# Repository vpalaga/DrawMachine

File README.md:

# DrawMachine

**An XY pen plotter driven by a Raspberry Pi Pico and a home-made G-code dialect called FCODE.**

Feed it a `.dxf` drawing, it works out where the pen has to go, and a Pico steps three stepper motors (X, Y and a Z pen lift) to draw it on A4 paper.

> **The goal:** a 100% working, reliable XY plotter that does my homework.
> Partially based on the Scrabble bot.

---

## How it works

```mermaid
flowchart LR
    A[".dxf drawing"] --> B["FCODEgenerator<br/>Python"]
    B --> C[".FCODE file<br/>absolute positions in mm"]
    C --> D["DataSendToPico<br/>Python, over USB serial"]
    D --> E["Pico firmware<br/>C++, relative steps"]
    E --> F["TMC2209 drivers<br/>X, Y, Z steppers"]
```

1. **`FCODEgenerator`** reads a DXF (or you script the pen by hand), centres it on the paper, reorders the strokes to minimise pen travel, and writes an `.FCODE` text file. Positions are in **millimetres**.
2. **`DataSendToPico`** reads the FCODE file line by line, converts millimetres to motor steps, range-checks every move and sends one command at a time to the Pico over USB CDC (virtual serial port). It waits for the Pico to confirm each command.
3. **`StepperDriver-pico`** is the firmware. It parses each command, coordinates X and Y step pulses so both axes finish a move together, lifts and lowers the pen, and homes against the end switches.

---

## Repository layout

| Path | What's in it |
| --- | --- |
| `FCODEgenerator/` | DXF reader, path optimiser, FCODE writer and preview renderer (Python) |
| `FCODEgenerator/dxfexamples/` | Sample DXF files to try |
| `DataSendToPico/` | Host-side sender: file runner, mm to steps conversion, serial transport, test CLI and GUI (Python) |
| `StepperDriver-pico/` | Pico firmware (C++ / Pico SDK) |
| `StepperDriver-pico/Pico_pins_map.txt` | ASCII Pico pinout showing which GPIO does what |
| `StepperDriver-pico/bresenham_test.py` | Draws the step pattern of the line algorithm with PIL, used to design the move function |
| `pcb/2.0/DrawMv2.0/` | **Current board**: KiCad project for the v2.0 controller PCB |
| `pcb/test/` | Retired first prototype board (v1), kept for reference only |
| `pcb2_0_schematic.pdf` | PDF of the v2.0 schematic |
| `images/` | Documentation images |

---

## Hardware

- **Controller:** Raspberry Pi Pico (USB CDC serial to the PC).
- **Drivers:** three **TMC2209** stepper drivers, one each for X, Y and Z. Microstepping is set on the board with switches, and the host software assumes **8x**.
- **Motion:** 200 steps/rev steppers on 2 mm pitch rods, so the host uses **800 steps per mm** (200 x 8 microsteps / 2 mm).
- **Pen lift:** the Z stepper raises and lowers the pen. The default stroke is 6500 steps and can be changed with `SZS`.
- **Limit switches:** one each for X, Y and Z, used for calibration. Each limit-switch input has an external 4.7 kΩ pull-up resistor.
- **Work area:** A4 landscape, 297 x 210 mm (A5 and A3 are also defined in the generator).
- **Indicators:** an "instruction" LED (lit while commands are arriving) and a "console mode" LED.
- **Board extras (v2.0):** 6 A fuse and bulk capacitor on the motor supply, status LEDs and a debug header.

### Pin map (from `motorDriver.cpp`)

A full ASCII drawing of the Pico with every pin is in [`StepperDriver-pico/Pico_pins_map.txt`](StepperDriver-pico/Pico_pins_map.txt).

| Function | GPIO |
| --- | --- |
| X stepper: STEP / DIR / EN | 13 / 12 / 10 |
| Y stepper: STEP / DIR / EN | 8 / 6 / 9 |
| Z stepper: STEP / DIR / EN | 4 / 3 / 5 |
| End switch X / Y / Z | 11 / 7 / 2 |
| Extra buttons B1 / B2 | 18 / 17 |
| LED instruction / console mode | 15 / 14 |

The limit switches connect their GPIO inputs to GND when pressed. The firmware also enables the Pico's internal pull-ups; the external 4.7 kΩ pull-ups were added to stabilize the switch signals. Motor enable pins are active low.

---

## Getting started

### 1. Build and flash the firmware

Requirements: Pico SDK 2.2.0, CMake 3.13+, the ARM GNU toolchain (the CMake file is set up for the VS Code Pico extension).

```bash
cd StepperDriver-pico
mkdir build && cd build
cmake ..
make -j
```

Hold **BOOTSEL**, plug the Pico in, and copy `motorDriver.uf2` onto the drive that appears. On boot the console LED blinks six times.

`CMakeLists.txt` defaults to `PICO_BOARD pico`. If you are using a Pico 2 / Pico 2 W, configure with `cmake -DPICO_BOARD=pico2_w ..` (or `pico2`).

### 2. Install the Python dependencies

Python **3.10+** is required (the code uses `match` and `X | Y` type hints). Run this command from the repository root:

```bash
pip install -r requirements.txt
```

The GUI also needs `tkinter`, which ships with most Python installers.

### 3. Generate an FCODE file

Run from inside `FCODEgenerator/` (the modules import each other without a package prefix):

```bash
cd FCODEgenerator
```

```python
from main import FGenerator

gen = FGenerator("dxfexamples/simpleShape.dxf",
                 acc=0.1,          # curve flattening accuracy in mm
                 text=False,       # True = also draw TEXT / MTEXT as outlines
                 optimize=True,    # reorder strokes to cut pen travel
                 join_tol=0.5)     # points closer than this (mm) count as the same point

gen.generate_instructions()
gen.save(show_visualization=True)  # writes .fcodes/simpleShape.FCODE and opens a preview
```

The preview draws pen-down moves in black, pen-up travel in red and the paper outline in blue, so you can check placement before anything moves.

### 4. Plot it

Plug the Pico in **before** starting Python, then:

```bash
cd DataSendToPico
python -c "from src.Controller import Controller; Controller('../FCODEgenerator/.fcodes/simpleShape.FCODE').do_file()"
```

This runs the `.FCODE` file generated above. The controller initializes the pen head, homes X and Y with `CLB`, then moves the carriage to the configured paper-origin offset. Make sure the carriage has room to move before you run it.

---

## FCODE

### File format

An FCODE file is plain text: a header, then one instruction per line.

```
header_length 3
name simpleShape
plane_size_mm (297, 210)
MOV 10.0 10.0
PDN
MOV 10.0 200.0
MOV 287.0 200.0
MOV 287.0 10.0
MOV 10.0 10.0
PUP
MOV 76.54 127.03
PDN
MOV 88.93 142.52
...
```

- `header_length` is the number of header lines (including itself). The sender skips that many lines.
- `MOV x y` in a file is an **absolute position in mm**, measured from the bottom-left corner of the paper. Coordinates are rounded to 0.01 mm.
- The pen starts up, so the first stroke begins with a travel `MOV` followed by `PDN`.

### Instructions

| Instruction | Args | Meaning | Where it runs |
| --- | --- | --- | --- |
| `MOV x y` | 2 | Move the head to (x, y) in mm. Draws if the pen is down | Host converts to relative steps, Pico executes |
| `PUP` | 0 | Pen up | Pico |
| `PDN` | 0 | Pen down | Pico |
| `WAT s` | 1 | Wait *s* seconds | Pico |
| `CLB` | 0 | Calibrate X and Y against their end switches. The host then moves to the paper-origin offset and zeroes its position | Host and Pico |
| `HCB` | 0 | Calibrate Z (pen head) only | Pico |
| `SZS steps` | 1 | Set the pen up/down stroke length in steps (1-50000) | Pico |
| `HOM` | 0 | `HCB`, then move to the home position `(0, 300)` mm | **Host only** |
| `SCM m` | 1 | Set console mode (0, 1 or 2) | Pico (used internally by the sender) |

`PDN` returns an error if the firmware already considers the pen down. `PUP` runs the lift and endstop-seek sequence. The generator avoids emitting redundant pen-state instructions.

### Automatic recalibration

To fight lost steps on long jobs, the generator inserts `HCB` every 200 instructions and `CLB` every 1000 (`head_calibration_after_instruction` and `overall_calibration_after_instruction`).

### Writing FCODE by hand

`FGenerator` also works without a DXF. Run this from `FCODEgenerator/`, pass a name instead of a `.dxf` path, and drive the pen yourself:

```python
from main import FGenerator
from gen import PAPER_SIZES

w, h = PAPER_SIZES["A4"]
gen = FGenerator("outline_A4", text=False, optimize=True, join_tol=0.5)

gen.draw_to(0, h)
gen.draw_to(w, h)
gen.draw_to(w, 0)
gen.draw_to(0, 0)
gen.home()
gen.save()
```

Available calls: `pen_up`, `pen_down`, `move_to`, `travel_to` (pen up, then move), `draw_to` (pen down, then move), `draw_polyline`, `wait`, `head_calibrate`, `calibrate`, `home`, `save`. See `example_manual_instructions.py` for a 5000-segment random-walk example.

### Supported DXF content

`LINE`, `CIRCLE`, `ARC`, `ELLIPSE`, `LWPOLYLINE`, `POLYLINE`, `SPLINE`, `SOLID` / `TRACE` / `3DFACE`, `POINT` (drawn as a small circle), `TEXT` / `MTEXT` / `ATTRIB` (as outlines, only with `text=True`). Block references (`INSERT`) and `DIMENSION` entities are exploded. Anything else is skipped.

---

## Pico serial protocol

The Pico enumerates as a USB CDC serial device. The sender finds it by USB vendor ID `2E8A`.

- The host sends **one line per instruction**, terminated with `\n`, at most 127 characters.
- Arguments are separated by whitespace. On the wire `MOV` takes **relative steps**, not millimetres (`MOV 800 -1600` moves +1 mm in X and -2 mm in Y).
- For every line the Pico replies with **two lines**:
  1. **Receive status**, sent immediately: `0` = line understood, `1` = rejected (unknown instruction, wrong argument count, or a bad number). After a `1` there is no second reply.
  2. **Finish status**, sent when the instruction is done: `0` = OK, `1` = failed (for example a limit switch was never reached during calibration).
- If no instruction arrives for **3 seconds**, the instruction LED goes off and the motor drivers are disabled.

### Firmware behaviour

- **XY motion:** the axis with more steps determines the move duration; follow-axis pulses are distributed across that duration so both axes finish together.
- **Timing:** X/Y and Z pulse timing is configurable with `SMS`. The firmware defaults to 50 us half-cycles for X/Y and 100 us for Z; the host adjusts motor speed for each move.
- **Motor enables:** X/Y remain enabled while instructions are being processed and are disabled after 3 seconds without a new instruction. The Z motor is disabled after each pen movement.
- **Calibration:** `CLB` drives X and Y towards their switches; `HCB` moves Z away from its switch, then raises it back until the switch triggers. Every calibration loop has a step limit (400000 for XY, 50000 for Z) so a missing or miswired switch can't make it run forever.
- **Pen stroke length:** `SZS steps` sets the Z-axis down stroke and the reference length used for the fixed pen-up move and endstop seek.

---

## Host-side tools (`DataSendToPico/`)

| File | Purpose |
| --- | --- |
| `Controller.py` | Reads an FCODE file and runs it instruction by instruction, printing progress |
| `MotorController.py` | mm to steps conversion, host travel range checks (380 x 315 mm), paper-origin offset (A4 preset: 33 mm, 48 mm from the switches, so measure your own), request logging |
| `MotorOverclass.py` | Per-axis constants and position bookkeeping (steps per mm, max travel) |
| `CDC_send.py` | `Transmitter`: finds the Pico, sends commands and reads the two status replies, with a 200 s response timeout |
| `CDC_test.py` | Tiny CLI: type raw instructions such as `MOV 100 100` and see both replies |
| `CDC_gui.py` | Tkinter GUI for the same thing, with quick buttons for `CLB`, `HCB`, `PUP`, `PDN` |
| `settings.py` | `SPEED_MODE` (skips response validation) and other flags |
| `tools.py` | Coloured request timing/logging helpers |

---

## PCB

The controller board is **v2.0**, designed in KiCad (about 98 x 67 mm). It carries the Pico, three TMC2209 drivers (U1 to U3, one per axis), per-driver microstepping switches, end-switch inputs with 4.7 kΩ pull-ups, a fused motor supply (6 A fuse and a 330 uF bulk capacitor), status LEDs and a debug header. This is the board the firmware pin map targets.

- KiCad project: `pcb/2.0/DrawMv2.0/`
- Schematic PDF: `pcb2_0_schematic.pdf`

The v1 prototype in `pcb/test/` is no longer used and is kept only for reference. The `*-backups` folders are KiCad's automatic backups.

---

## Known issues and to-do

- [ ] Standard G-code support, which would be easier than maintaining FCODE.

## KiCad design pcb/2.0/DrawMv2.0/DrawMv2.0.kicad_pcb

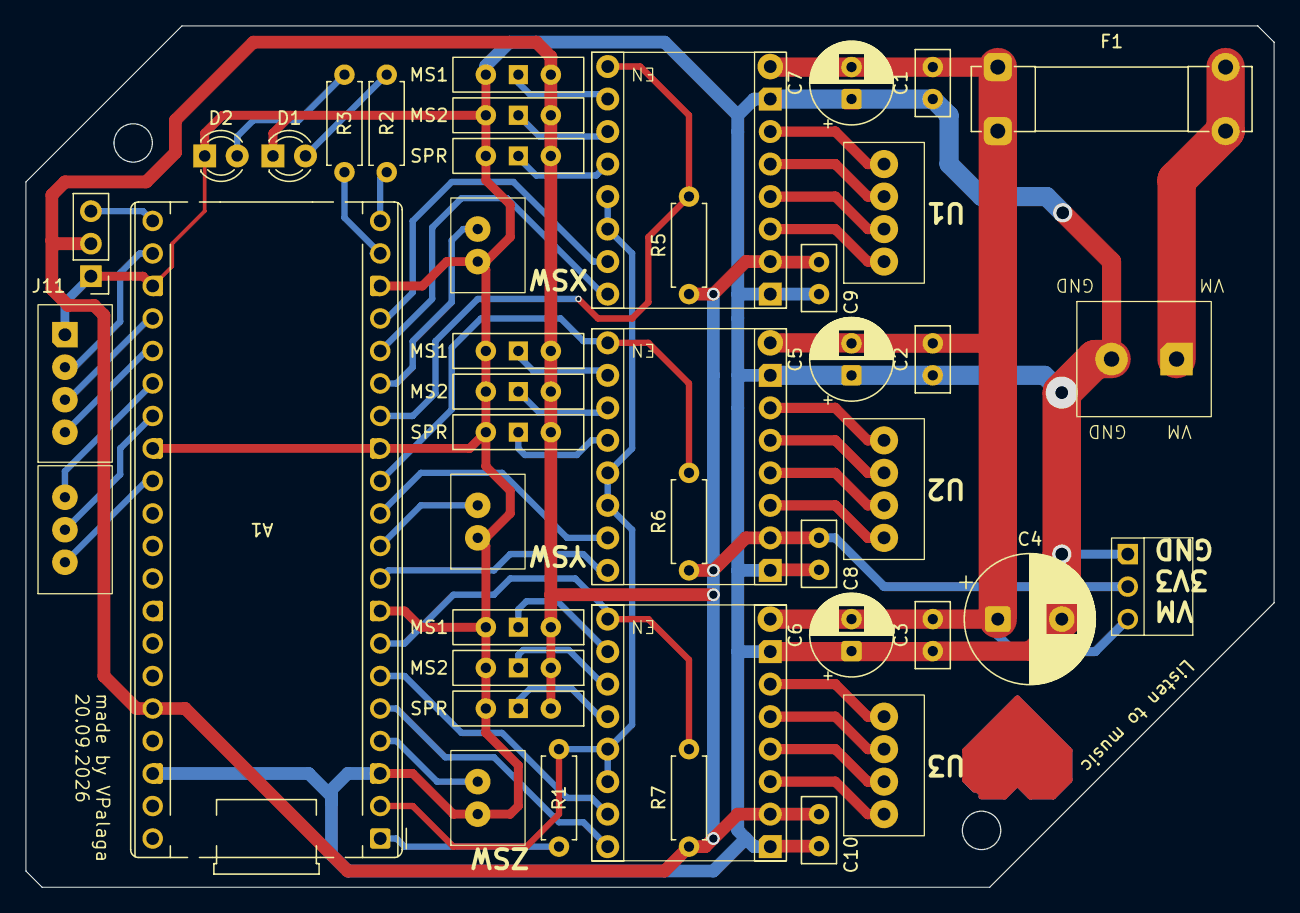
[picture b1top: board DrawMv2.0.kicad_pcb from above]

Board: 2 copper layers, 97.5 x 67.3 mm, 43 parts (0 on the bottom side), 50 nets.

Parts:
A1: RaspberryPi_Pico_W; RaspberryPi_Pico_Common_THT
C1, C2, C3, C8, C9, C10: 100nF; C_Disc_D5.0mm_W2.5mm_P2.50mm
C4: 330uF; CP_Radial_D10.0mm_P5.00mm
C5, C6, C7: 47uF; CP_Radial_D6.3mm_P2.50mm
D1, D2: SMALL; LED_D3.0mm
F1: 6A; Fuseholder_Clip-5x20mm_Bel_FC-203-22_Lateral_P17.80x5.00mm_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
J1: M1; 4pinTerminal
J2: M2; 4pinTerminal
J3: M3; 4pinTerminal
J4: PWR; Untitled
J5: X_SW; XH2pin
J6: Y_SW; XH2pin
J7: Z_SW; XH2pin
J8: Conn_01x03_Pin; XH3pin
J9: Conn_01x04_Pin; XH4pin
J10: debug
J11: Conn_01x03_Pin; PinHeader_1x03_P2.54mm_Vertical
MS1, MS1#2, MS1#3, MS2, MS2#2, MS2#3: SW_SPDT; SW_Slide-03_Wuerth-WS-SLTV_10x2.5x6.4_P2.54mm_ok
R1: 1K; R_Axial_DIN0207_L6.3mm_D2.5mm_P7.62mm_Horizontal
R2, R3: R_Axial_DIN0207_L6.3mm_D2.5mm_P7.62mm_Horizontal
R5, R6, R7: 10K; R_Axial_DIN0207_L6.3mm_D2.5mm_P7.62mm_Horizontal
SPR: SW_SPDT; SW_Slide-03_Wuerth-WS-SLTV_10x2.5x6.4_P2.54mm_ok
SPR#2, SPR#3: SW_SPDT; SW_Slide-03_Wuerth-WS-SLTV_10x2.5x6.4_P2.54mm_ok
U1, U2, U3: TMC2209

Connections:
/3V3: A1.36 (3V3), C8.1, C9.1, C10.1, J10.2, J11.2, MS1.1 (A), MS1#2.1 (A), MS1#3.1 (A), MS2.1 (A), MS2#2.1 (A), MS2#3.1 (A), R5.1, R6.1, R7.1, SPR.1 (A), SPR#2.1 (A), SPR#3.1 (A), U1.15 (VIO), U2.15 (VIO), U3.15 (VIO)
/24: F1.2, J4.2
/UART: A1.2 (GPIO1), R1.1, U1.5 (UART_TX), U1.6 (UART_RX), U2.5 (UART_TX), U2.6 (UART_RX), U3.5 (UART_TX), U3.6 (UART_RX)
/VM: C1.2, C2.2, C3.2, C4.1, C5.2, C6.2, C7.2, F1.1, J10.1, U1.9 (VM), U2.9 (VM), U3.9 (VM)
GND: A1.3 (GND), A1.8 (GND), A1.13 (GND), A1.18 (GND), A1.23 (GND), A1.28 (GND), A1.38 (GND), C1.1, C2.1, C3.1, C4.2, C5.1, C6.1, C7.1, C8.2, C9.2, C10.2, D1.1 (K), D2.1 (K), J4.1, J5.1, J6.1, J7.1, J9.4, J10.3, J11.1, MS1.3 (C), MS1#2.3 (C), MS1#3.3 (C), MS2.3 (C), MS2#2.3 (C), MS2#3.3 (C), SPR.3 (C), SPR#2.3 (C), SPR#3.3 (C), U1.10 (GND), U1.16 (GND), U2.10 (GND), U2.16 (GND), U3.10 (GND), U3.16 (GND)
unnamed: A1.1 (GPIO0), R1.2
unnamed: A1.4 (GPIO2), J6.2
unnamed: A1.5 (GPIO3), U3.8 (DIR)
unnamed: A1.6 (GPIO4), U3.7 (STEP)
unnamed: A1.7 (GPIO5), R7.2, U3.1 (EN)
unnamed: A1.9 (GPIO6), U2.8 (DIR)
unnamed: A1.10 (GPIO7), J7.2
unnamed: A1.11 (GPIO8), U2.7 (STEP)
unnamed: A1.12 (GPIO9), R6.2, U2.1 (EN)
unnamed: A1.14 (GPIO10), R5.2, U1.1 (EN)
unnamed: A1.15 (GPIO11), J5.2
unnamed: A1.16 (GPIO12), U1.8 (DIR)
unnamed: A1.17 (GPIO13), U1.7 (STEP)
unnamed: A1.19 (GPIO14), R3.1
unnamed: A1.20 (GPIO15), R2.1
unnamed: A1.21 (GPIO16), J11.3
unnamed: A1.22 (GPIO17), J9.3
unnamed: A1.24 (GPIO18), J9.2
unnamed: A1.25 (GPIO19), J9.1
unnamed: A1.26 (GPIO20), J8.3
unnamed: A1.27 (GPIO21), J8.2
unnamed: A1.29 (GPIO22), J8.1
unnamed: D1.2 (A), R2.2
unnamed: D2.2 (A), R3.2
unnamed: J1.1, U1.14 (M1B)
unnamed: J1.2, U1.13 (M1A)
unnamed: J1.3, U1.12 (M2A)
unnamed: J1.4, U1.11 (M2B)
unnamed: J2.1, U2.14 (M1B)
unnamed: J2.2, U2.13 (M1A)
unnamed: J2.3, U2.12 (M2A)
unnamed: J2.4, U2.11 (M2B)
unnamed: J3.1, U3.14 (M1B)
unnamed: J3.2, U3.13 (M1A)
unnamed: J3.3, U3.12 (M2A)
unnamed: J3.4, U3.11 (M2B)
unnamed: SPR#3.2 (B), U1.4 (SPREAD)
unnamed: MS2#2.2 (B), U1.3 (MS2)
unnamed: MS1#2.2 (B), U1.2 (MS1)
unnamed: SPR.2 (B), U2.4 (SPREAD)
unnamed: MS2#3.2 (B), U2.3 (MS2)
unnamed: MS1#3.2 (B), U2.2 (MS1)
unnamed: SPR#2.2 (B), U3.4 (SPREAD)
unnamed: MS2.2 (B), U3.3 (MS2)
unnamed: MS1.2 (B), U3.2 (MS1)

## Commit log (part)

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2025-12-22 add gitignore and lwpolyline generation and added main class to main
    new file: .idea/vcs.xml
    modified: FCODEgen/__pycache__/dxfReader.cpython-313.pyc
    modified: FCODEgen/__pycache__/main.cpython-313.pyc
    modified: FCODEgen/dxfReader.py
    modified: FCODEgen/file.FCODE
    deleted: FCODEgen/gtur.py
2025-12-22 test .FCODE ignore
2025-12-22 test .FCODE ignore ...
2025-12-22 test .FCODE ignore ....
2025-12-22 Ignore .FCODE files
2025-12-22 fix cash FCODE
2025-12-26 Add project description to README
    Add project overview and control details for robot.
2025-12-27 added main logic for MotorControll
2025-12-27 update reademe
2025-12-27 start with c
2026-02-10 Enhance README with FCODE and construction details
    Updated README with detailed sections on FCODE, Raspberry Pi, and construction specifications.
2026-02-12 Update README with robot and control system details
    Clarified robot description and added details about Z-axis and Raspberry Pico functionality.
2026-02-12 chnage the data structure
2026-02-12 updates on the swich driver
2026-02-12 rename and fix calibrate call
2026-02-12 sketch the c
2026-02-12 refractor the FCODE generator data structure
2026-02-12 remind my self to refractor schiwch driver to c
2026-02-13 Revise README with updated FCODE and construction info
    Updated README.md to reflect changes in FCODE examples, Raspberry Pi setup, and construction details.
2026-02-13 fixed the exaple useage
2026-02-13 Revise README with examples and instructions
    Updated examples and clarified instructions for Raspberry Pi and Pico integration.
2026-02-13 Fix formatting and update function reference in README
2026-02-13 add the raspberry pi cpp start module, with usb enable conifg
2026-02-14 refractor Swich handler from .py to .cpp
2026-02-14 working swich setup
2026-02-14 add LED class
    when swich pressed, the leds comply
2026-02-14 add Stepper Class (working)
2026-02-14 full rotation spinn
2026-02-14 work on CDC connection
2026-02-14 work on send protocoll
2026-02-15 string CDC socket
2026-02-15 work on CDC protocol
2026-02-15 change Instruction Types to 3 upper letter only
    "MOVE": -> "MOV"
    "PENUP": ->"PUP"
    "PENDOWN"->"PDN"
    "WAIT" ->"WAT"
    "CALIBRATE" ->"CLB"
2026-02-16 get_instruction_details function (untested)
2026-02-16 added instruction paths
2026-02-16 fix arguments size cherck bug, (2h - fuck this shit)
2026-02-16 measure instruction send, recive confirmation time ~1ms - very happy
2026-02-16 fix typo
2026-02-17 create stepper driver (cpp and py) python tested
2026-02-17 fix Bresenham-style move function bug
2026-02-17 Document StepperDriver class and Bresenham function
    Added documentation for the StepperDriver class and its Bresenham move function.
2026-02-17 add images and Bresenham-style move function pic
2026-02-17 Add image for Bresenham move function
    Added an image of the Bresenham move function to the README.
2026-02-17 code calibrate and test, add instruction led
2026-02-17 rm .idea and add to .gitignore
2026-02-17 add display driver
2026-02-18 add PCA9685 driver (untested)
2026-02-18 review python motor driver and fix bugs and connect it to cdc send_recive func
2026-02-18 add servo instructions to pico
2026-02-19 test and implement controller, get first FCODE file running on one stepper (second not avalible)
2026-02-19 add penis init screen
2026-02-28 change servo protocol and add manual instructions
2026-03-01 add console mode
2026-03-01 add console mode (c++)
2026-03-01 add give pos button
2026-03-01 add speed profile
2026-03-01 fix manual movement pos output
2026-03-01 speed profile bug fixes
2026-03-15 i dont know anymore...
2026-04-12 fix typos and accord gpio pinout on pico
2026-04-16 add automatic port finding: - W: untested - not for linux
2026-04-16 add movew to starting offset
2026-04-16 added separat tmc setting and test buttons and accord them to real
2026-04-16 - change speed profile - find FCODE generator bug: circle x center is moved by + cca 1cm has been a problem before, bruteforce it?
2026-04-17 - add pcb files - vibe remake dxf reader (gpt) -> fixed the offset bug
2026-06-24 add drivers
2026-06-24 integrate the drivers
